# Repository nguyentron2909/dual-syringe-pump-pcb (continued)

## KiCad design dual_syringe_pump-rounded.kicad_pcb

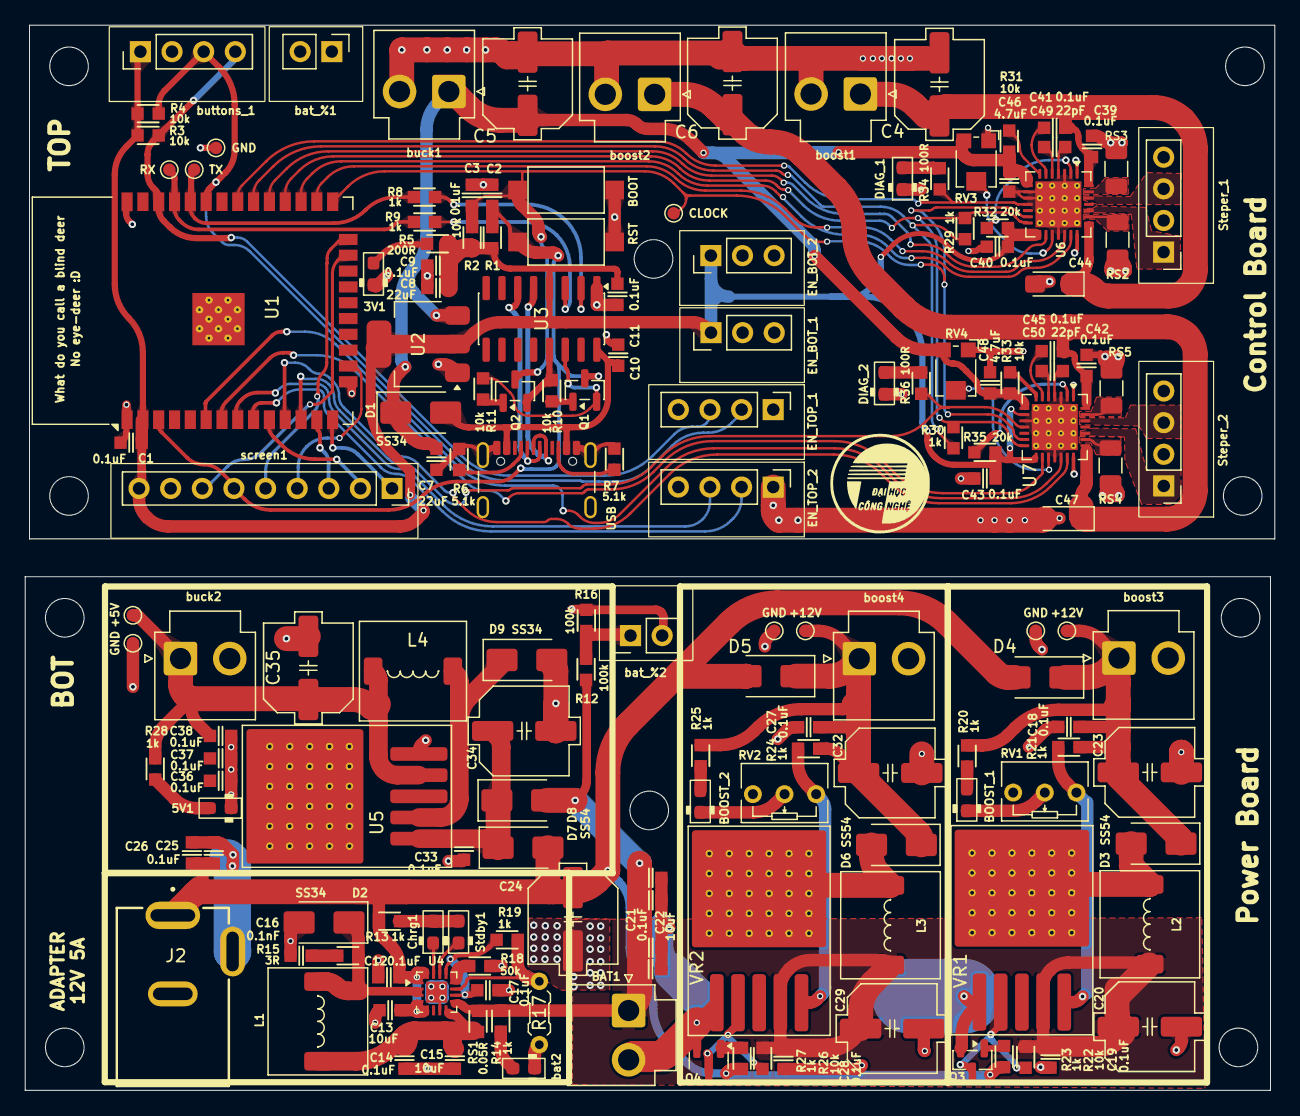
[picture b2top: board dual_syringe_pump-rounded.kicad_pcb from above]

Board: 2 copper layers, 100.3 x 85.5 mm, 161 parts (0 on the bottom side), 94 nets.

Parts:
3V1, 5V1: LED; LED_0603_1608Metric_Pad1.05x0.95mm
+5V, +12V, +12V#2: TestPoint; TestPoint_Pad_D1.0mm
BAT1: Bat_protected; JST_VH_B2P-VH-B_1x02_P3.96mm_Vertical
BOOST_1, BOOST_2: LED; LED_0603_1608Metric_Pad1.05x0.95mm
BOOT: reset; SW_SPST_CK_RS282G05A3
C1, C2, C3, C9, C10, C11, C12, C14, C17, C18, C19, C21, C25, C26, C27, C28, C30, C33, C36, C37, C38, C39, C40, C41, C42, C43, C45: 0.1uF; C_0603
C4, C5, C6, C23, C24, C32, C34, C35: 100uF; C_Elec_6.3x7.7
C7, C8: 22uF; C_0603
C13, C15, C22, C31: 10uF; C_0603
C16: 0.1nF; C_0603
C20, C29: 330uF; C_Elec_6.3x7.7
C44, C47: 100uF; CP_EIA-3216-12_Kemet-S_HandSolder
C46, C48: 4.7uF; C_0603
C49, C50: 22pF; C_0603
CLOCK: TestPoint; TestPoint_Pad_D1.0mm
Chrg1: LED; LED_0603_1608Metric_Pad1.05x0.95mm
D1, D2, D9: SS34; D_SMA
D3, D4, D5, D6, D7, D8: SS54; D_SMA
DIAG_1, DIAG_2: LED; LED_0603_1608Metric_Pad1.05x0.95mm
EN_BOT_1, EN_BOT_2: Conn_01x03; PinHeader_1x03_P2.54mm_Vertical
EN_TOP_1, EN_TOP_2: Conn_01x04; PinHeader_1x04_P2.54mm_Vertical
GND: TestPoint; TestPoint_Pad_D1.0mm
GND#2, GND#3, GND#4: TestPoint; TestPoint_Pad_D1.0mm
J2: Barrel_Jack_Switch_Pin3Ring; GCT_DCJ200-10-A-XX-K_REVA
L1: 22uH; L_7.3x7.3_H4.5
L2, L3: 47uH; L_7.3x7.3_H4.5
L4: 33uH; L_7.3x7.3_H4.5
Q1, Q2, Q3, Q4: SS8050; SOT-23
R1, R2, R3, R4, R10, R11, R22, R26, R31, R33: 10k; R_0603
R5: 200R; R_0603
R6, R7: 5.1k; R_0603
R8, R9, R13, R14, R19, R20, R21, R23, R24, R25, R27, R28, R29, R30: 1k; R_0603
R12, R16: 100k; R_0603
R15: 3R; R_0603
R17: 47d 3950 (10K); R_Axial_DIN0204_L3.6mm_D1.6mm_P5.08mm_Horizontal
R18: 50k; R_0603
R32, R35: 20k; R_0603
R34, R36: 100R; R_0603
RS1: 0.05R; R_0603
RS2, RS3, RS4, RS5: 0.1R; R_1206_3216Metric
RST: boot; SW_SPST_CK_RS282G05A3
RV1, RV2: 10k; Potentiometer_Bourns_3266Y_Vertical
RV3, RV4: 20k; Potentiometer_Bourns_TC33X_Vertical
RX: TestPoint; TestPoint_Pad_D1.0mm
Stdby1: LED; LED_0603_1608Metric_Pad1.05x0.95mm
Steper_1, Steper_2: Conn_01x04; PinHeader_1x04_P2.54mm_Vertical
TX: TestPoint; TestPoint_Pad_D1.0mm
U1: ESP32-WROOM-32
U2: AMS1117-3.3; SOT-223-3_TabPin2
U3: CH340C; SOIC-16_3.9x9.9mm_P1.27mm
U4: TP5100; LQFN-16-1EP_3x3mm_P0.5mm_EP1.7x1.7mm
U5: LM2596S-buck; TO-263-5_TabPin3_ThermalVias
U6, U7: TMC2209-LA; VQFN-28-1EP_5x5mm_P0.5mm_EP3.7x3.7mm_ThermalVias
USB: USB_C_Receptacle_USB2.0_16P; USB_C_Receptacle_GCT_USB4105-xx-A_16P_TopMnt_Horizontal
VR1, VR2: XL6019; TO-263-5_TabPin6_ThermalVias
bat2: LED; LED_0603_1608Metric_Pad1.05x0.95mm
bat_%1, bat_%2: battery _percentage; PinHeader_1x02_P2.54mm_Vertical
boost1, boost3: boost_1; JST_VH_B2P-VH-B_1x02_P3.96mm_Vertical
boost2, boost4: boost_2; JST_VH_B2P-VH-B_1x02_P3.96mm_Vertical
buck1, buck2: buck; JST_VH_B2P-VH-B_1x02_P3.96mm_Vertical
buttons_1: Conn_01x04; PinHeader_1x04_P2.54mm_Vertical
screen1: Conn_01x09_Pin; PinSocket_1x09_P2.54mm_Vertical

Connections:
+3.3V: C1.1, C8.1, C9.1, C11.1, C40.2, C43.2, EN_BOT_1.1, EN_BOT_2.1, R1.1, R2.1, R3.1, R4.1, R5.2, R32.1, R35.1, U1.2 (VDD), U2.2 (VO), U3.4 (V3), U6.15 (VCC_IO), U7.9 (MS1/AD0), U7.15 (VCC_IO), buttons_1.1, screen1.9
+5V: +5V.1, C5.1, C7.1, C35.1, C36.1, C37.1, C38.1, C46.2, C48.2, D1.1 (K), L4.2, R28.2, R31.1, R33.1, RV3.3, RV4.3, U2.3 (VI), U5.4 (FB), U6.8 (5VOUT), U7.8 (5VOUT), buck1.1, buck2.1
+12V_1: +12V#2.1, C4.1, C18.1, C23.1, C39.1, C41.1, C44.1, D3.1 (K), D4.1 (K), R20.2, R21.2, U6.22 (VS), U6.28 (VS), boost1.1, boost3.1
+12V_2: +12V.1, C6.1, C27.1, C32.1, C42.1, C45.1, C47.1, D5.1 (K), D6.1 (K), R24.2, R25.2, U7.22 (VS), U7.28 (VS), boost2.1, boost4.1
/BACKLIGHT: U1.10 (IO25), screen1.2
/CS: U1.23 (IO15), screen1.7
/D+: U3.5 (UD+), USB.A6 (D+), USB.B6 (D+)
/D-: U3.6 (UD-), USB.A7 (D-), USB.B7 (D-)
/DC: U1.24 (IO2), screen1.5
/DTR: Q2.2 (E), R10.1, U3.13 (~DTR)
/MISO: U1.14 (IO12), screen1.1
/MOSI: U1.16 (IO13), screen1.4
/Power Circuits/NTC: R17.2 (-), R19.2, U4.11 (TS)
/Power Circuits/Vreg: C17.1, R19.1, U4.10 (VREG), U4.13 (CS)
/RST: Q1.2 (E), R11.2, U3.14 (~RTS)
/RX: R9.2, RX.1, U1.35 (TXD0/IO1)
/SCK: U1.13 (IO14), screen1.3
/SCL: EN_TOP_1.3, R3.2, U1.36 (IO22), buttons_1.4
/SCL1: EN_TOP_2.3, U1.8 (IO32)
/SDA: EN_TOP_1.2, R4.2, U1.33 (IO21), buttons_1.3
/SDA1: EN_TOP_2.2, U1.9 (IO33)
/TX: R8.2, TX.1, U1.34 (RXD0/IO3)
/esp_EN: C2.1, Q1.3 (C), R1.2, RST.1, U1.3 (EN), screen1.6
Adapter_+12V: C12.1, C13.1, C24.1, C25.1, C26.1, D4.2 (A), D5.2 (A), D7.2 (A), J2.1, R13.1, R23.2, R27.2, U4.1 (VIN), U4.4 (VIN), U4.5 (VIN), U4.16 (VIN)
DIAG_1: R34.2, U1.31 (IO19), U6.11 (DIAG)
DIAG_2: R36.2, U1.12 (IO27), U7.11 (DIAG)
DIR_1: U1.26 (IO4), U6.19 (DIR)
DIR_2: U1.6 (IO34), U7.19 (DIR)
EN_1: U1.27 (IO16), U6.20 (STDBY)
EN_2: U1.11 (IO26), U7.20 (STDBY)
GND: 5V1.1 (K), BAT1.2 (-), BOOST_1.1 (K), BOOST_2.1 (K), C12.2, C13.2, C14.2, C15.2, C16.2, C17.2, C18.2, C19.2, C20.2, C21.2, C22.2, C23.2, C24.2, C25.2, C26.2, C27.2, C28.2, C29.2, C30.2, C31.2, C32.2, C33.2, C34.2, C35.2, C36.2, C37.2, C38.2, D2.2 (A), D9.2 (A), GND#2.1, GND#3.1, GND#4.1, J2.2, J2.3, Q3.2 (E), Q4.2 (E), R16.2, R17.1 (+), R18.1, RV1.2, RV2.2, U4.7 (GND), U4.17 (EXP), U5.3 (GND), U5.5 (~ON/OFF), VR1.1 (GND), VR2.1 (GND), bat2.1 (K), bat_%2.2, boost3.2, boost4.2, buck2.2
GND1: 3V1.1 (K), BOOT.2, C1.2, C2.2, C3.2, C4.2, C5.2, C6.2, C7.2, C8.2, C9.2, C10.2, C11.2, C39.2, C40.1, C42.2, C43.1, C44.2, C46.1, C47.2, C48.1, DIAG_1.1 (K), DIAG_2.1 (K), EN_BOT_1.3, EN_BOT_2.3, EN_TOP_1.1, EN_TOP_2.1, GND.1, R6.1, R7.2, RS2.2, RS3.2, RS4.2, RS5.2, RST.2, RV3.1, RV4.1, U1.1 (GND), U1.15 (GND), U1.38 (GND), U1.39 (GND), U2.1 (GND), U3.1 (GND), U6.3 (GND), U6.9 (MS1/AD0), U6.10 (MS2/AD1), U6.18 (GND), U6.29 (GND), U7.3 (GND), U7.10 (MS2/AD1), U7.18 (GND), U7.29 (GND), USB.A1 (GND), USB.A12 (GND), USB.B1 (GND), USB.B12 (GND), USB.S1 (SHIELD), boost1.2, boost2.2, buck1.2, buttons_1.2, screen1.8
unnamed: 3V1.2 (A), R5.1
unnamed: 5V1.2 (A), R28.1
unnamed: BOOST_1.2 (A), R20.1
unnamed: BOOST_2.2 (A), R25.1
unnamed: C16.1, R15.1
unnamed: Chrg1.2 (A), R13.2, Stdby1.2 (A)
unnamed: Chrg1.1 (K), U4.15 (~CHRG)
unnamed: D2.1 (K), L1.1, R15.2, U4.2 (LX), U4.3 (LX)
unnamed: D3.2 (A), L2.2, VR1.3 (SW), VR1.6 (SW)
unnamed: D6.2 (A), L3.2, VR2.3 (SW), VR2.6 (SW)
unnamed: C33.1, C34.1, D7.1 (K), D8.1 (K), U5.1 (VIN)
unnamed: D9.1 (K), L4.1, U5.2 (OUT)
unnamed: DIAG_1.2 (A), R34.1
unnamed: DIAG_2.2 (A), R36.1
unnamed: R6.2, USB.A5 (CC1)
unnamed: R7.1, USB.B5 (CC2)
unnamed: Q1.1 (B), R10.2
unnamed: Q2.1 (B), R11.1
unnamed: Q3.1 (B), R23.1
unnamed: Q3.3 (C), R22.1, VR1.2 (EN)
unnamed: Q4.1 (B), R27.1
unnamed: Q4.3 (C), R26.1, VR2.2 (EN)
unnamed: Stdby1.1 (K), U4.14 (~STDBY)
unnamed: Steper_1.1, U6.24 (OA1)
unnamed: Steper_1.2, U6.21 (OA2)
unnamed: Steper_1.3, U6.26 (OB1)
unnamed: Steper_1.4, U6.1 (OB2)
unnamed: Steper_2.1, U7.24 (OA1)
unnamed: Steper_2.2, U7.21 (OA2)
unnamed: Steper_2.3, U7.26 (OB1)
unnamed: Steper_2.4, U7.1 (OB2)
unnamed: R9.1, U3.3 (RXD)
unnamed: R8.1, U3.2 (TXD)
unnamed: R18.2, U4.12 (RTRICK)
unnamed: C14.1, C15.1, L1.2, RS1.2, U4.8 (VS)
unnamed: RS2.1, U6.23 (BRA)
unnamed: RS3.1, U6.27 (BRB)
unnamed: C49.2, U6.5 (CPI)
unnamed: C49.1, U6.4 (CPO)
unnamed: R31.2, U6.7 (SPREAD)
unnamed: C41.2, U6.6 (VCP)
unnamed: RV3.2, U6.17 (VREF)
unnamed: R32.2, U6.2 (~EN)
unnamed: RS4.1, U7.23 (BRA)
unnamed: RS5.1, U7.27 (BRB)
unnamed: C50.2, U7.5 (CPI)
unnamed: C50.1, U7.4 (CPO)
unnamed: R33.2, U7.7 (SPREAD)
unnamed: C45.2, U7.6 (VCP)
unnamed: RV4.2, U7.17 (VREF)
unnamed: R35.2, U7.2 (~EN)
unnamed: R21.1, RV1.3, VR1.5 (FB)
unnamed: R24.1, RV2.3, VR2.5 (FB)
unnamed: R14.1, bat2.2 (A)
unnamed: R12.2, R16.1, bat_%2.1
RX_TMC: R29.2, R30.2, U1.28 (IO17), U6.14 (~PD/UART), U7.14 (~PD/UART)
STEP_1: U1.29 (IO5), U6.16 (STEP)
STEP_2: U1.7 (IO35), U7.16 (STEP)
TX_TMC: R29.1, R30.1, U1.30 (IO18)
USB_5V: C10.1, D1.2 (A), U3.16 (VCC), USB.A4 (VBUS), USB.A9 (VBUS), USB.B4 (VBUS), USB.B9 (VBUS)
Vbat: BAT1.1 (+), C19.1, C20.1, C21.1, C22.1, C28.1, C29.1, C30.1, C31.1, D8.2 (A), L2.1, L3.1, R12.1, R14.2, R22.2, R26.2, RS1.1, U4.9 (BAT), VR1.4 (VIN), VR2.4 (VIN)
esp32_CLK: BOOT.1, C3.1, CLOCK.1, Q2.3 (C), R2.2, U1.25 (IO0), U6.13 (CLK), U7.13 (CLK)

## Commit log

2026-02-22 update - 22-Feb-26
2026-02-22 Highlighted connectors
2026-02-22 added pictures
2026-02-22 Enhance README with images and PCB layout section
    Updated README with additional images and modified project structure section.
2026-03-20 changed to mouse bites
2026-05-10 post production fixes
